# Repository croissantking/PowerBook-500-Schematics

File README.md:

# Macintosh PowerBook 500 Series CPU Card Schematics

The PowerBook 500 Series is a very popular laptop with hobbyists. Lately I have been tinkering a lot with mine. Unfortunately no schematics are available which limits repair and modding potential. In an effort to remedy this, I studied a CPU card with a multimeter and drew up schematics in KiCad.

The CPU card is essentially identical across all five models: the 520, 520c, 540, 540c and 550c.

The drawings are a work in progress so I expect there to be some errors, although hopefully just minor ones.

Follow this link to jump to the [PDF Schematics Directory](https://github.com/croissantking/PowerBook-500-Schematics/tree/main/docs).

### Acknowledgements

With thanks to oldcrap.org for permission to re-use their PowerBook 540c CPU card scans.

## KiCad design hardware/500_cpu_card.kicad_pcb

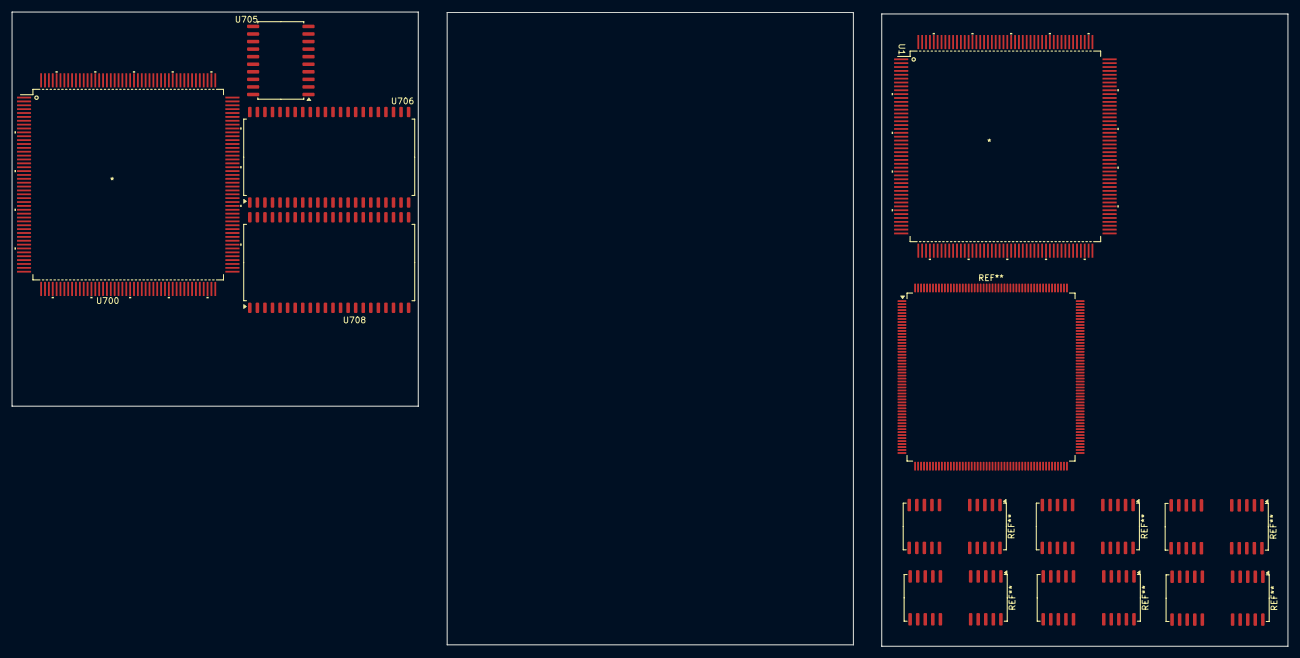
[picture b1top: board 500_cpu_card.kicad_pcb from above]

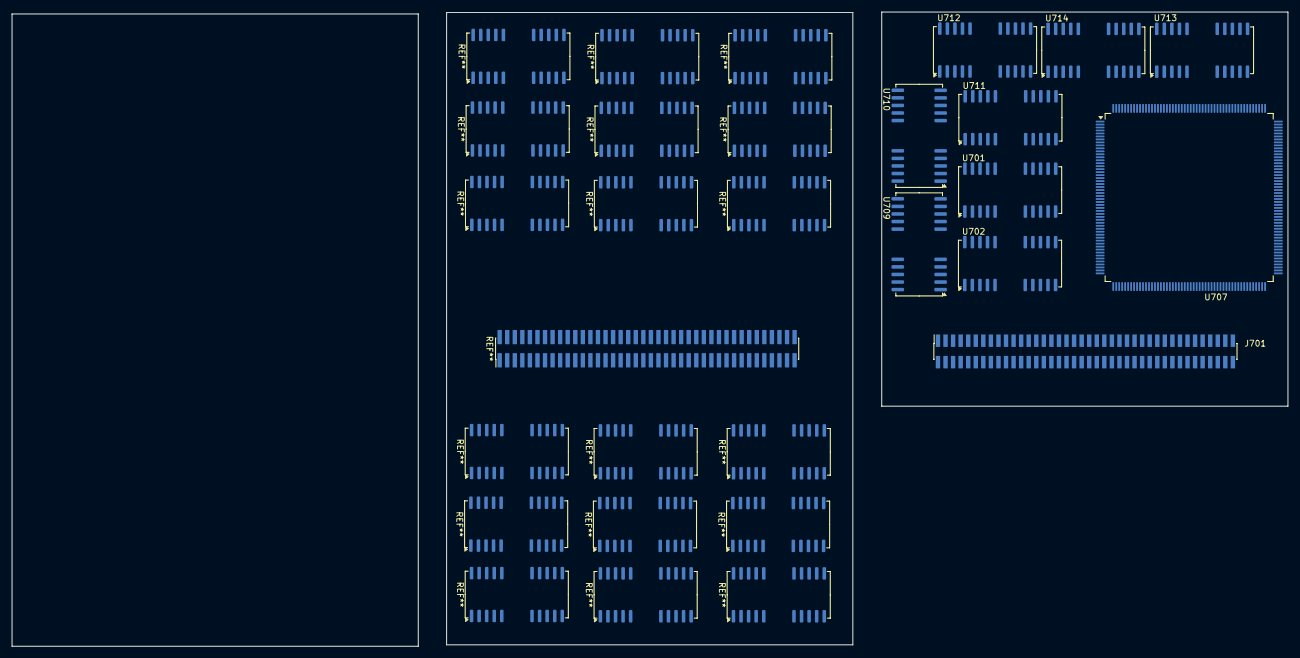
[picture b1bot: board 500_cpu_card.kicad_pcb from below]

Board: 6 copper layers, 214.3 x 106.5 mm, 15 parts (10 on the bottom side), 161 nets, no tracks yet.

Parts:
J701: System Interconnect; PinSocket_2x40_P1.27mm_Vertical_SMD
U1: MC68040FE; Mot_QFP184_HandSolder
U700: XC68LC040FE25/33; Mot_QFP184_HandSolder
U701, U702, U709, U710, U711, U712, U713, U714: DRAM 1Mx4; SOJ-26
U705: MC88921; SOIC-20W_7.5x12.8mm_P1.27mm
U706, U708: ROM 1Mx16; SOP-44_12.6x28.5mm_P1.27mm
U707: Pratt Memory Controller/Bus Translator; PQFP-208_28x28mm_P0.5mm

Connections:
+5V: J701.13 (VCC), J701.32 (VCC), J701.49 (VCC), J701.68 (VCC), U701.13 (VDD), U702.13 (VDD), U706.23 (VCC), U706.33 (BYTE), U707.1 (VCC), U707.52 (VCC), U707.53 (VCC), U707.79 (VCC), U707.104 (VCC), U707.105 (VCC), U707.156 (VCC), U707.157 (VCC), U707.181 (VCC), U707.208 (VCC), U708.23 (VCC), U708.33 (BYTE), U709.13 (VDD), U710.13 (VDD), U711.13 (VDD), U712.13 (VDD), U713.13 (VDD), U714.13 (VDD)
+5V_CPU: U700.9 (VCC), U700.10 (~MDIS), U700.11 (~CDIS), U700.19 (VCC), U700.21 (VCC), U700.29 (~TCI), U700.32 (VCC), U700.43 (VCC), U700.49 (VCC), U700.56 (VCC), U700.62 (VCC), U700.69 (VCC), U700.75 (VCC), U700.81 (VCC), U700.88 (VCC), U700.94 (VCC), U700.100 (VCC), U700.102 (VCC), U700.109 (VCC), U700.115 (VCC), U700.122 (VCC), U700.128 (VCC), U700.136 (VCC), U700.143 (VCC), U700.149 (VCC), U700.155 (VCC), U700.161 (VCC), U700.168 (VCC), U700.175 (VCC), U700.181 (VCC)
/Page 2/IO_69: J701.69 (?), U707.171 (IO_69)
/Page 2/IO_70: J701.70 (?), U707.170 (IO_70)
/Page 2/IO_A0: J701.2 (030_A0), U707.4 (IO_A0)
/Page 2/IO_A1: J701.3 (030_A1), U707.6 (IO_A1)
/Page 2/IO_A2: J701.4 (030_A2), U707.8 (IO_A2)
/Page 2/IO_A3: J701.5 (030_A3), U707.10 (IO_A3)
/Page 2/IO_A4: J701.6 (030_A4), U707.12 (IO_A4)
/Page 2/IO_A5: J701.7 (030_A5), U707.14 (IO_A5)
/Page 2/IO_A6: J701.10 (030_A6), U707.16 (IO_A6)
/Page 2/IO_A7: J701.9 (030_A7), U707.18 (IO_A7)
/Page 2/IO_A8: J701.12 (030_A8), U707.20 (IO_A8)
/Page 2/IO_A9: J701.11 (030_A9), U707.22 (IO_A9)
/Page 2/IO_A10: J701.14 (030_A10), U707.31 (IO_A10)
/Page 2/IO_A11: J701.15 (030_A11), U707.33 (IO_A11)
/Page 2/IO_A12: J701.16 (030_A12), U707.35 (IO_A12)
/Page 2/IO_A13: J701.17 (030_A13), U707.37 (IO_A13)
/Page 2/IO_A14: J701.18 (030_A14), U707.39 (IO_A14)
/Page 2/IO_A15: J701.19 (030_A15), U707.41 (IO_A15)
/Page 2/IO_A16: J701.22 (030_A16), U707.43 (IO_A16)
/Page 2/IO_A17: J701.21 (030_A17), U707.45 (IO_A17)
/Page 2/IO_A18: J701.24 (030_A18), U707.47 (IO_A18)
/Page 2/IO_A19: J701.23 (030_A19), U707.49 (IO_A19)
/Page 2/IO_A20: J701.26 (030_A20), U707.56 (IO_A20)
/Page 2/IO_A21: J701.27 (030_A27), U707.58 (IO_A21)
/Page 2/IO_A22: J701.28 (030_A22), U707.60 (IO_A22)
/Page 2/IO_A23: J701.29 (030_A23), U707.62 (IO_A23)
/Page 2/IO_A24: J701.30 (030_A24), U707.64 (IO_A24)
/Page 2/IO_A25: J701.31 (030_A25), U707.66 (IO_A25)
/Page 2/IO_A26: J701.34 (030_A36), U707.68 (IO_A26)
/Page 2/IO_A27: J701.33 (030_A27), U707.70 (IO_A27)
/Page 2/IO_A28: J701.36 (030_A28), U707.72 (IO_A28)
/Page 2/IO_A29: J701.35 (030_A29), U707.74 (IO_A29)
/Page 2/IO_A30: J701.38 (030_A30), U707.81 (IO_A30)
/Page 2/IO_A31: J701.39 (030_A31), U707.83 (IO_A31)
/Page 2/IO_CLK: J701.71 (IO_CLK), U707.173 (IO_CLK)
/Page 2/IO_D16: J701.46 (030_D16), U707.101 (IO_D16)
/Page 2/IO_D17: J701.43 (030_D17), U707.103 (IO_D17)
/Page 2/IO_D18: J701.48 (030_D18), U707.108 (IO_D18)
/Page 2/IO_D19: J701.45 (030_D19), U707.110 (IO_D19)
/Page 2/IO_D20: J701.50 (030_D20), U707.112 (IO_D20)
/Page 2/IO_D21: J701.47 (030_D21), U707.114 (IO_D21)
/Page 2/IO_D22: J701.52 (030_D22), U707.116 (IO_D22)
/Page 2/IO_D23: J701.51 (030_D23), U707.118 (IO_D23)
/Page 2/IO_D24: J701.54 (030_D24), U707.120 (IO_D24)
/Page 2/IO_D25: J701.53 (030_D25), U707.122 (IO_D25)
/Page 2/IO_D26: J701.58 (030_D26), U707.124 (IO_D26)
/Page 2/IO_D27: J701.55 (030_D27), U707.126 (IO_D27)
/Page 2/IO_D28: J701.60 (030_D28), U707.128 (IO_D28)
/Page 2/IO_D29: J701.57 (030_D29), U707.133 (IO_D29)
/Page 2/IO_D30: J701.62 (030_D30), U707.135 (IO_D30)
/Page 2/IO_D31: J701.59 (030_D31), U707.137 (IO_D31)
/Page 2/IO_SIZ0: J701.42 (030_SIZ0), U707.162 (IO_SIZ0)
/Page 2/IO_SIZ1: J701.41 (030_SIZ1), U707.163 (IO_SIZ1)
/Page 2/~AS: J701.66 (~AS), U707.159 (~AS)
/Page 2/~BERR: J701.67 (~BERR), U707.169 (~BERR)
/Page 2/~BGACK: J701.72 (~BGACK), U707.172 (~BGACK)
/Page 2/~DSACK0: J701.64 (~DSACK0), U707.164 (~DSACK0)
/Page 2/~DSACK1: J701.63 (~DSACK1), U707.165 (~DSACK1)
/Page 2/~DS: J701.65 (~DS), U707.160 (~DS)
/Page 2/~IO_IPL0: J701.74 (~030_IPL0), U707.166 (~IO_IPL0)
/Page 2/~IO_IPL1: J701.75 (~030_IPL1), U707.167 (~IO_IPL1)
/Page 2/~IO_IPL2: J701.76 (~030_IPL2), U707.168 (~IO_IPL2)
/Page 2/~IO_RESET: J701.79 (~IO_RESET), U707.154 (~IO_RESET)
/Page 2/~MDM_RESET: J701.78 (~MDM_RESET), U707.155 (~MDM_RESET)
/Page 3/A0: U701.9 (A0), U702.9 (A0), U709.9 (A0), U710.9 (A0), U711.9 (A0), U712.9 (A0), U713.9 (A0), U714.9 (A0)
/Page 3/A1: U701.10 (A1), U702.10 (A1), U709.10 (A1), U710.10 (A1), U711.10 (A1), U712.10 (A1), U713.10 (A1), U714.10 (A1)
/Page 3/A2: U701.11 (A2), U702.11 (A2), U709.11 (A2), U710.11 (A2), U711.11 (A2), U712.11 (A2), U713.11 (A2), U714.11 (A2)
/Page 3/A3: U701.12 (A3), U702.12 (A3), U709.12 (A3), U710.12 (A3), U711.12 (A3), U712.12 (A3), U713.12 (A3), U714.12 (A3)
/Page 3/A4: U701.14 (A4), U702.14 (A4), U709.14 (A4), U710.14 (A4), U711.14 (A4), U712.14 (A4), U713.14 (A4), U714.14 (A4)
/Page 3/A5: U701.15 (A5), U702.15 (A5), U709.15 (A5), U710.15 (A5), U711.15 (A5), U712.15 (A5), U713.15 (A5), U714.15 (A5)
/Page 3/A6: U701.16 (A6), U702.16 (A6), U709.16 (A6), U710.16 (A6), U711.16 (A6), U712.16 (A6), U713.16 (A6), U714.16 (A6)
/Page 3/A7: U701.17 (A7), U702.17 (A7), U709.17 (A7), U710.17 (A7), U711.17 (A7), U712.17 (A7), U713.17 (A7), U714.17 (A7)
/Page 3/A8: U701.18 (A8), U702.18 (A8), U709.18 (A8), U710.18 (A8), U711.18 (A8), U712.18 (A8), U713.18 (A8), U714.18 (A8)
/Page 3/A9: U701.5 (A9), U702.5 (A9), U709.5 (A9), U710.5 (A9), U711.5 (A9), U712.5 (A9), U713.5 (A9), U714.5 (A9)
/Page 3/~DRAM_CAS0: U713.23 (~CAS), U714.23 (~CAS)
/Page 3/~DRAM_CAS1: U711.23 (~CAS), U712.23 (~CAS)
/Page 3/~DRAM_CAS2: U709.23 (~CAS), U710.23 (~CAS)
/Page 3/~DRAM_CAS3: U701.23 (~CAS), U702.23 (~CAS)
/Page 3/~DRAM_RAS0: U701.4 (~RAS), U702.4 (~RAS), U709.4 (~RAS), U710.4 (~RAS), U711.4 (~RAS), U712.4 (~RAS), U713.4 (~RAS), U714.4 (~RAS)
/Page 3/~DRAM_WE: U701.3 (~WE), U702.3 (~WE), U709.3 (~WE), U710.3 (~WE), U711.3 (~WE), U712.3 (~WE), U713.3 (~WE), U714.3 (~WE)
/~ROM_CE: U706.12 (~CE), U708.12 (~CE)
/~ROM_OE: U706.14 (~OE), U708.14 (~OE)
A0: U700.70 (A0), U706.11 (A0), U707.3 (A0), U708.11 (A0)
A1: U700.71 (A1), U706.10 (A1), U707.5 (A1), U708.10 (A1)
A2: U700.73 (A2), U706.9 (A2), U707.7 (A2), U708.9 (A2)
A3: U700.74 (A3), U706.8 (A3), U707.9 (A3), U708.8 (A3)
A4: U700.76 (A4), U706.7 (A4), U707.11 (A4), U708.7 (A4)
A5: U700.77 (A5), U706.6 (A5), U707.13 (A5), U708.6 (A5)
A6: U700.79 (A6), U706.5 (A6), U707.15 (A6), U708.5 (A6)
A7: U700.80 (A7), U706.4 (A7), U707.17 (A7), U708.4 (A7)
A8: U700.82 (A8), U706.42 (A8), U707.19 (A8), U708.42 (A8)
A9: U700.83 (A9), U706.41 (A9), U707.21 (A9), U708.41 (A9)
A10: U700.173 (A10), U706.40 (A10), U707.30 (A10), U708.40 (A10)
A11: U700.172 (A11), U706.39 (A11), U707.32 (A11), U708.39 (A11)
A12: U700.170 (A12), U706.38 (A12), U707.34 (A12), U708.38 (A12)
A13: U700.169 (A13), U706.37 (A13), U707.36 (A13), U708.37 (A13)
A14: U700.167 (A14), U706.36 (A14), U707.38 (A14), U708.36 (A14)
A15: U700.166 (A15), U706.35 (A15), U707.40 (A15), U708.35 (A15)
A16: U700.164 (A16), U706.34 (A16), U707.42 (A16), U708.34 (A16)
A17: U700.163 (A17), U706.3 (A17), U707.44 (A17), U708.3 (A17)
A18: U700.160 (A18), U706.2 (A18), U707.46 (A18), U708.2 (A18)
A19: U700.159 (A19), U706.43 (A19), U707.48 (A19), U708.43 (A19)
A20: U700.157 (A20), U707.55 (A20)
A21: U700.156 (A21), U707.57 (A21)
A22: U700.154 (A22), U707.59 (A22)
A23: U700.153 (A23), U707.61 (A23)
A24: U700.151 (A24), U707.63 (A24)
A25: U700.150 (A25), U707.65 (A25)
A26: U700.148 (A26), U707.67 (A26)
A27: U700.147 (A27), U707.69 (A27)
A28: U700.145 (A28), U707.71 (A28)
A29: U700.144 (A29), U707.73 (A29)
A30: U700.142 (A30), U707.80 (A30)
A31: U700.141 (A31), U707.82 (A31)
D0: U700.138 (D0), U701.25 (DQ4), U706.15 (D0), U707.84 (D0)
D1: U700.137 (D1), U701.24 (DQ3), U706.17 (D1), U707.85 (D1)
D2: U700.134 (D2), U701.1 (DQ1), U706.19 (D2), U707.86 (D2)
D3: U700.133 (D3), U701.2 (DQ2), U706.21 (D3), U707.87 (D3)
D4: U700.131 (D4), U702.25 (DQ4), U706.24 (D4), U707.88 (D4)
D5: U700.129 (D5), U702.24 (DQ3), U706.26 (D5), U707.89 (D5)
D6: U700.127 (D6), U702.1 (DQ1), U706.28 (D6), U707.90 (D6)
D7: U700.126 (D7), U702.2 (DQ2), U706.30 (D7), U707.91 (D7)
D8: U700.124 (D8), U706.16 (D8), U707.92 (D8), U709.25 (DQ4)
D9: U700.123 (D9), U706.18 (D9), U707.93 (D9), U709.24 (DQ3)
D10: U700.120 (D10), U706.20 (D10), U707.94 (D10), U709.1 (DQ1)
D11: U700.119 (D11), U706.22 (D11), U707.95 (D11), U709.2 (DQ2)
D12: U700.117 (D12), U706.25 (D12), U707.96 (D12), U710.25 (DQ4)
D13: U700.116 (D13), U706.27 (D13), U707.97 (D13), U710.24 (DQ3)
D14: U700.114 (D14), U706.29 (D14), U707.98 (D14), U710.1 (DQ1)
D15: U700.113 (D15), U706.31 (A-1/D15), U707.99 (D15), U710.2 (DQ2)
D16: U700.111 (D16), U707.100 (D16), U708.15 (D0), U711.25 (DQ4)
D17: U700.110 (D17), U707.102 (D17), U708.17 (D1), U711.24 (DQ3)
D18: U700.107 (D18), U707.107 (D18), U708.19 (D2), U711.1 (DQ1)
D19: U700.106 (D19), U707.109 (D19), U708.21 (D3), U711.2 (DQ2)
D20: U700.104 (D20), U707.111 (D20), U708.24 (D4), U712.25 (DQ4)
D21: U700.103 (D21), U707.113 (D21), U708.26 (D5), U712.24 (DQ3)
D22: U700.101 (D22), U707.115 (D22), U708.28 (D6), U712.1 (DQ1)
D23: U700.99 (D23), U707.117 (D23), U708.30 (D7), U712.2 (DQ2)
D24: U700.97 (D24), U707.119 (D24), U708.16 (D8), U713.25 (DQ4)
D25: U700.96 (D25), U707.121 (D25), U708.18 (D9), U713.24 (DQ3)
D26: U700.93 (D26), U707.123 (D26), U708.20 (D10), U713.1 (DQ1)
D27: U700.92 (D27), U707.125 (D27), U708.22 (D11), U713.2 (DQ2)
D28: U700.90 (D28), U707.127 (D28), U708.25 (D12), U714.25 (DQ4)
D29: U700.89 (D29), U707.132 (D29), U708.27 (D13), U714.24 (DQ3)
D30: U700.87 (D30), U707.134 (D30), U708.29 (D14), U714.1 (DQ1)
D31: U700.86 (D31), U707.136 (D31), U708.31 (A-1/D15), U714.2 (DQ2)
GND: J701.1 (GND), J701.8 (GND), J701.20 (GND), J701.25 (GND), J701.37 (GND), J701.44 (GND), J701.56 (GND), J701.61 (GND), J701.73 (GND), J701.80 (GND), U700.5 (GND), U700.8 (GND), U700.16 (GND), U700.17 (GND), U700.20 (GND), U700.22 (GND), U700.24 (GND), U700.25 (GND), U700.27 (GND), U700.28 (GND), U700.30 (~AVEC), U700.33 (GND), U700.34 (SC0), U700.35 (SC1), U700.40 (GND), U700.46 (GND), U700.52 (GND), U700.55 (GND), U700.59 (GND), U700.65 (GND), U700.68 (GND), U700.72 (GND), U700.78 (GND), U700.84 (GND), U700.85 (GND), U700.91 (GND), U700.95 (GND), U700.98 (GND), U700.105 (GND), U700.108 (GND), U700.112 (GND), U700.118 (GND), U700.121 (GND), U700.125 (GND), U700.130 (GND), U700.132 (GND), U700.135 (GND), U700.139 (GND), U700.140 (GND), U700.146 (GND), U700.152 (GND), U700.158 (GND), U700.162 (GND), U700.165 (GND), U700.171 (GND), U700.174 (GND), U700.178 (GND), U700.184 (GND), U701.22 (OE), U701.26 (VSS), U702.22 (OE), U702.26 (VSS), U706.13 (GND), U706.32 (GND), U707.2 (GND), U707.23 (GND), U707.24 (GND), U707.27 (GND), U707.28 (GND), U707.29 (GND), U707.54 (GND), U707.76 (GND), U707.77 (GND), U707.78 (GND), U707.106 (GND), U707.129 (GND), U707.130 (GND), U707.131 (GND), U707.158 (GND), U707.182 (GND), U707.183 (GND), U707.184 (GND), U707.204 (GND), U707.205 (GND), U707.206 (GND), U708.13 (GND), U708.32 (GND), U709.22 (OE), U709.26 (VSS), U710.22 (OE), U710.26 (VSS), U711.22 (OE), U711.26 (VSS), U712.22 (OE), U712.26 (VSS), U713.22 (OE), U713.26 (VSS), U714.22 (OE), U714.26 (VSS)
R/~W: U700.58 (R/~W), U707.141 (R/~W)
SIZ0: U700.60 (SIZ0), U707.142 (SIZ0)
SIZ1: U700.54 (SIZ1), U707.143 (SIZ1)
~BB: U700.47 (~BB), U707.150 (~BB)
~BCLK: U700.18 (BCLK), U707.152 (BCLK)
~BG: U700.36 (~BG), U707.149 (~BG)
~BR: U700.50 (~BR), U707.148 (~BR)
~RSTI: U700.12 (~RSTI), U707.151 (~RSTI)
~TA: U700.38 (~TA), U707.139 (~TA)
~TBI: U700.31 (~TBI), U707.147 (~TBI)
~TEA: U700.37 (~TEA), U707.140 (~TEA)
~TS: U700.48 (~TS), U707.138 (~TS)
